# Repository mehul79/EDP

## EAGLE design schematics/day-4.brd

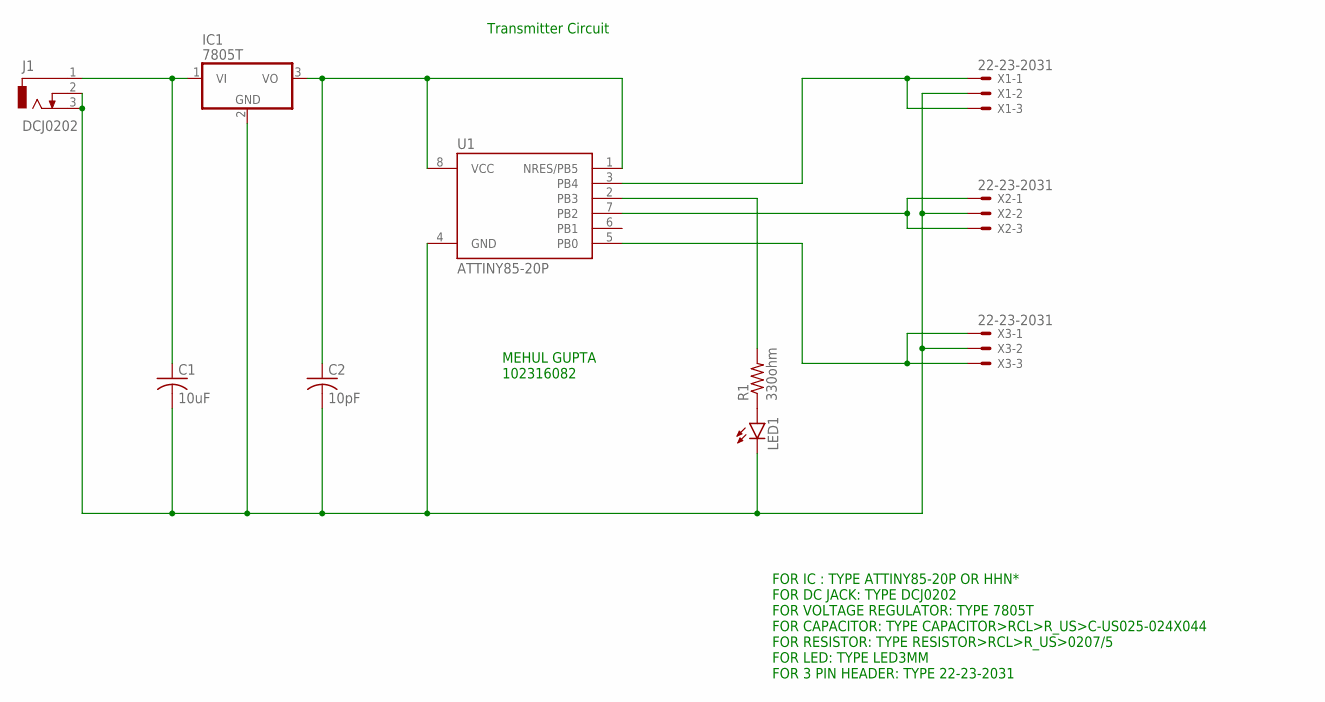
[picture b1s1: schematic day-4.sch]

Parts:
C1: 10uF; C025-024X044
C2: 10pF; C025-024X044
IC1: 7805T; TO220H
J1: DCJ0202
LED1: LED3MM
R1: 330ohm; 0204/5
U1: ATTINY85-20P; PDIP08_300MIL
X1, X2, X3: 22-23-2031

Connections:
unnamed: C1.1, IC1.1 (VI), J1.1
unnamed: C1.2, C2.2, IC1.2 (GND), J1.2, J1.3, LED1.K (C), U1.4 (GND), X1.2, X2.2, X3.2
unnamed: C2.1, IC1.3 (VO), U1.1 (NRES/PB5), U1.8 (VCC)
unnamed: U1.3 (PB4), X1.1, X1.3
unnamed: LED1.A, R1.1
unnamed: U1.7 (PB2), X2.1, X2.3
unnamed: R1.2, U1.2 (PB3)
unnamed: U1.5 (PB0), X3.1, X3.3

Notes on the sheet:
FOR IC : TYPE ATTINY85-20P OR HHN* FOR DC JACK: TYPE DCJ0202 FOR VOLTAGE REGULATOR: TYPE 7805T FOR CAPACITOR: TYPE CAPACITOR>RCL>R_US>C-US025-024X044 FOR RESISTOR: TYPE RESISTOR>RCL>R_US>0207/5 FOR LED: TYPE LED3MM FOR 3 PIN HEADER: TYPE 22-23-2031
Transmitter Circuit
MEHUL GUPTA 102316082

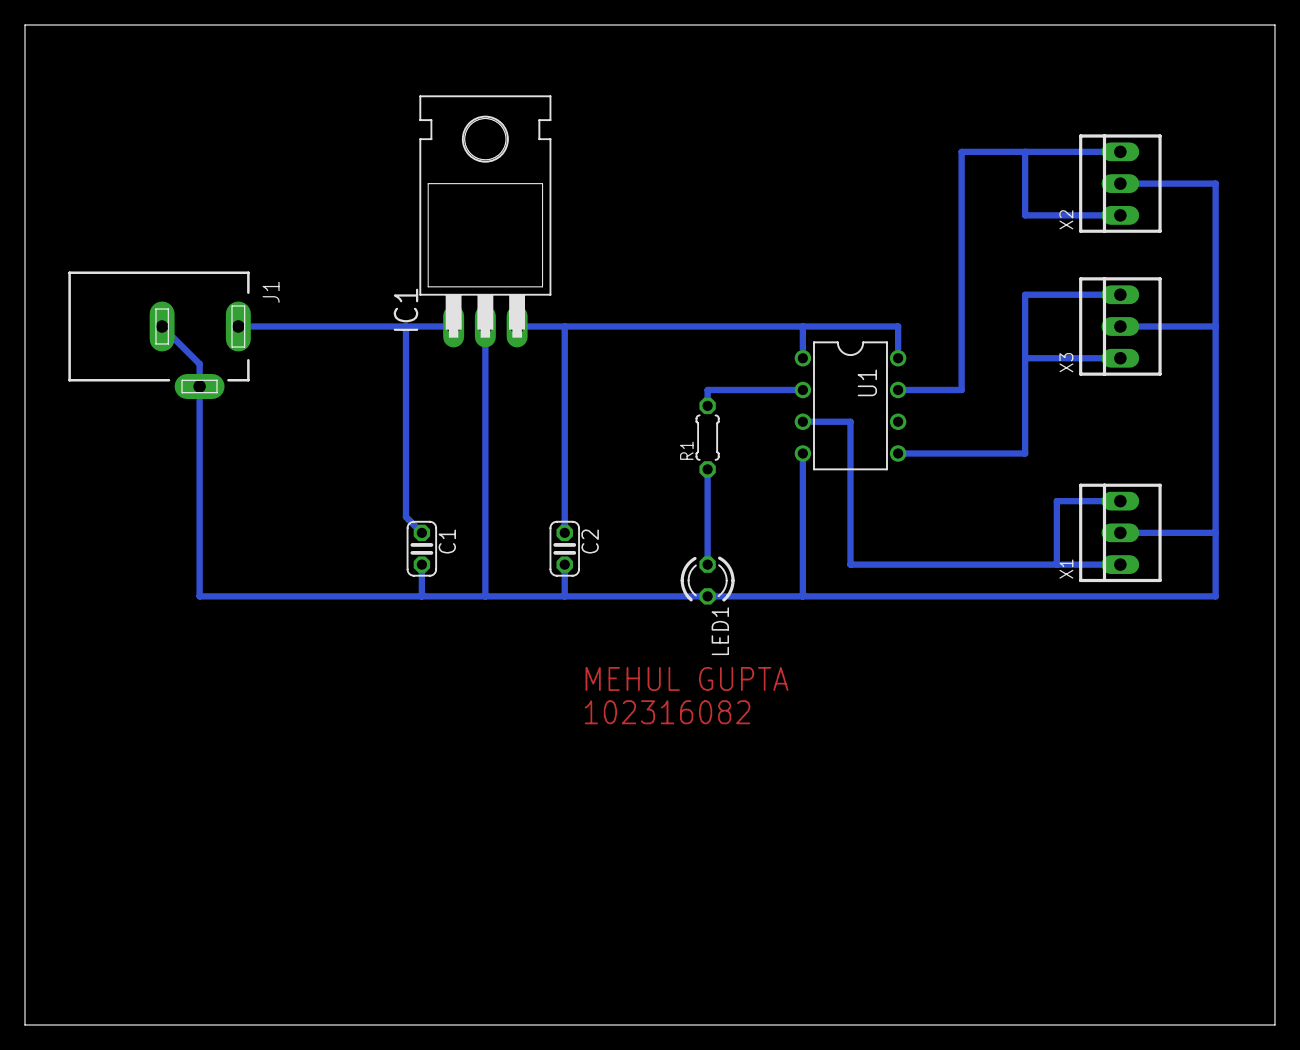
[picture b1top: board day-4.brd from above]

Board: 2 copper layers, 100.0 x 80.0 mm, 10 parts (0 on the bottom side), 8 nets.

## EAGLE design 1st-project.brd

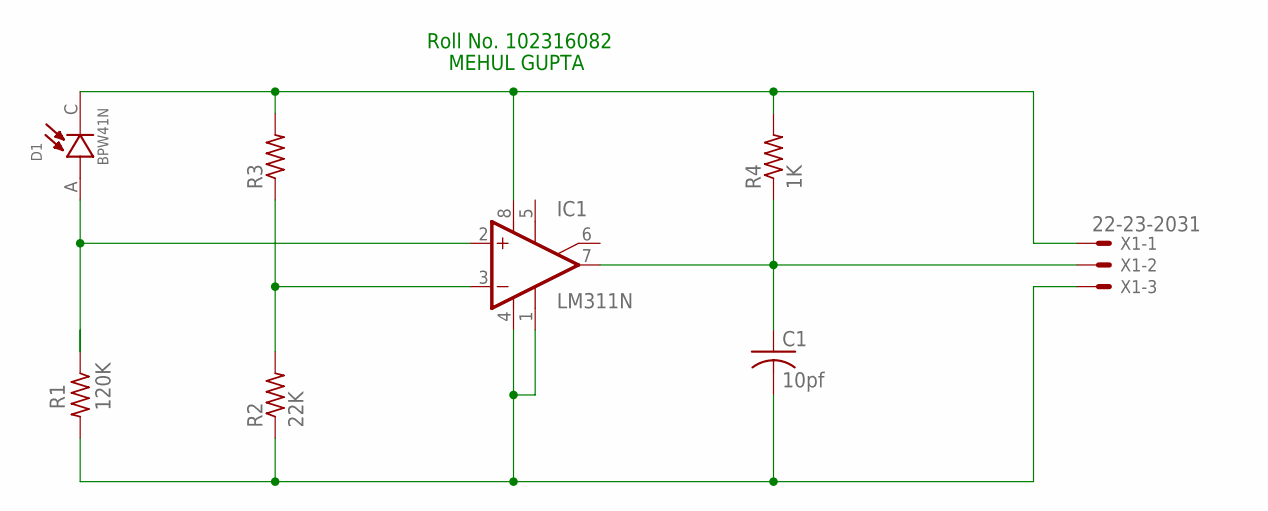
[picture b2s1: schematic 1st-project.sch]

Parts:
C1: 10pf; C025-024X044
D1: BPW41N; DIO_BPW41N
IC1: LM311N; DIL08
R1: 120K; 0204/5
R2: 22K; 0204/5
R3: R-US_0204/5; 0204/5
R4: 1K; 0204/5
X1: 22-23-2031

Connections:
unnamed: D1.A, IC1.2 (+IN), R1.1
unnamed: D1.C, IC1.8 (V+), R3.2, R4.2, X1.1
unnamed: C1.2, IC1.1 (GND), IC1.4 (V-), R1.2, R2.1, X1.3
unnamed: IC1.3 (-IN), R2.2, R3.1
unnamed: C1.1, IC1.7 (OUT), R4.1, X1.2

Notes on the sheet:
MEHUL GUPTA
Roll No. 102316082

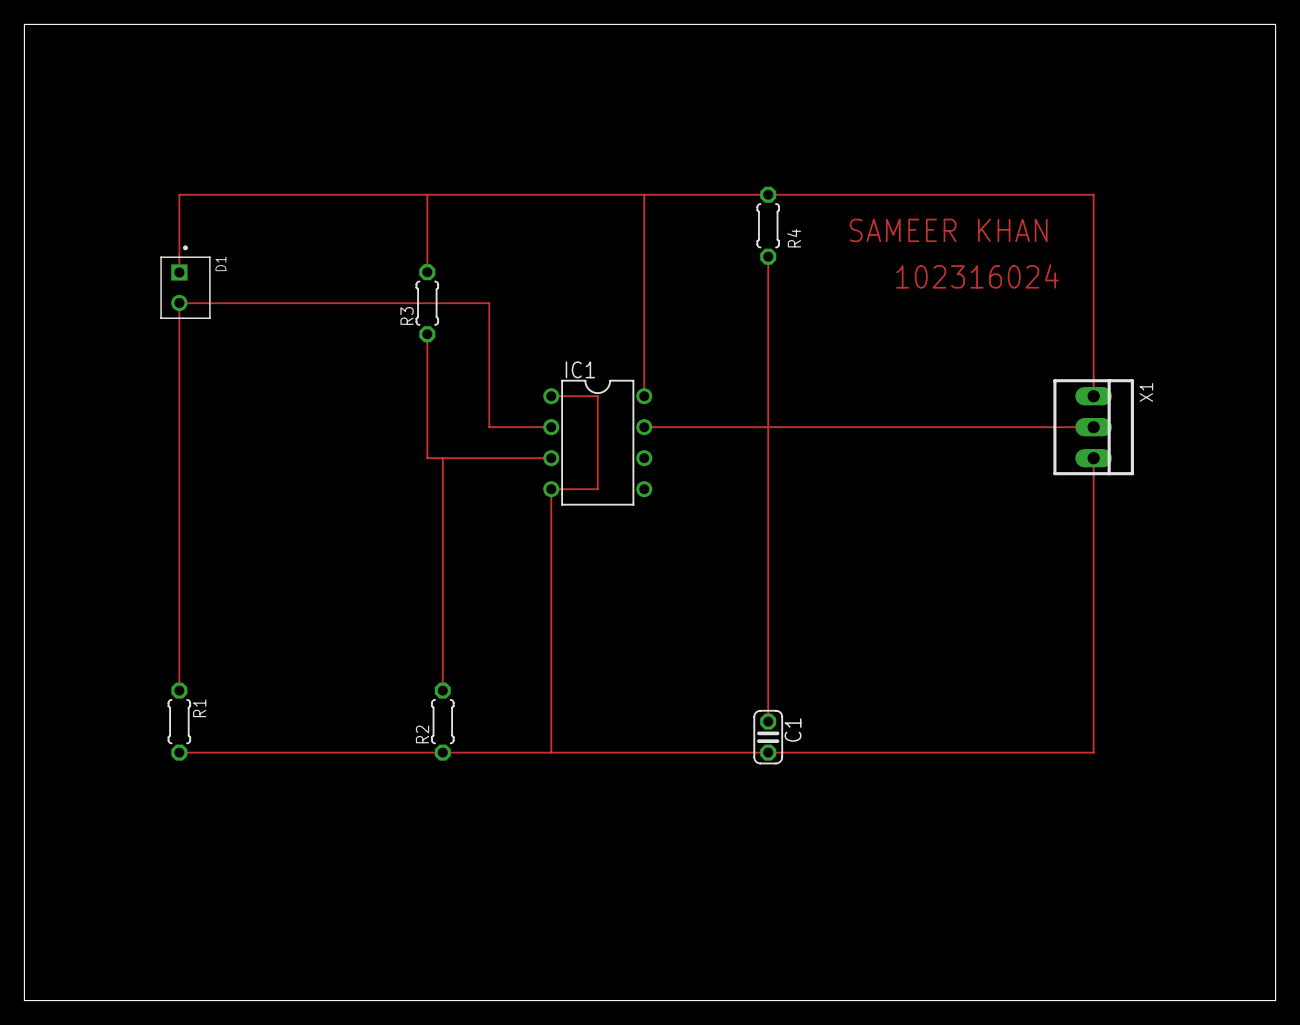
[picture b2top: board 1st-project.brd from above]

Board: 2 copper layers, 102.5 x 80.0 mm, 8 parts (0 on the bottom side), 5 nets.

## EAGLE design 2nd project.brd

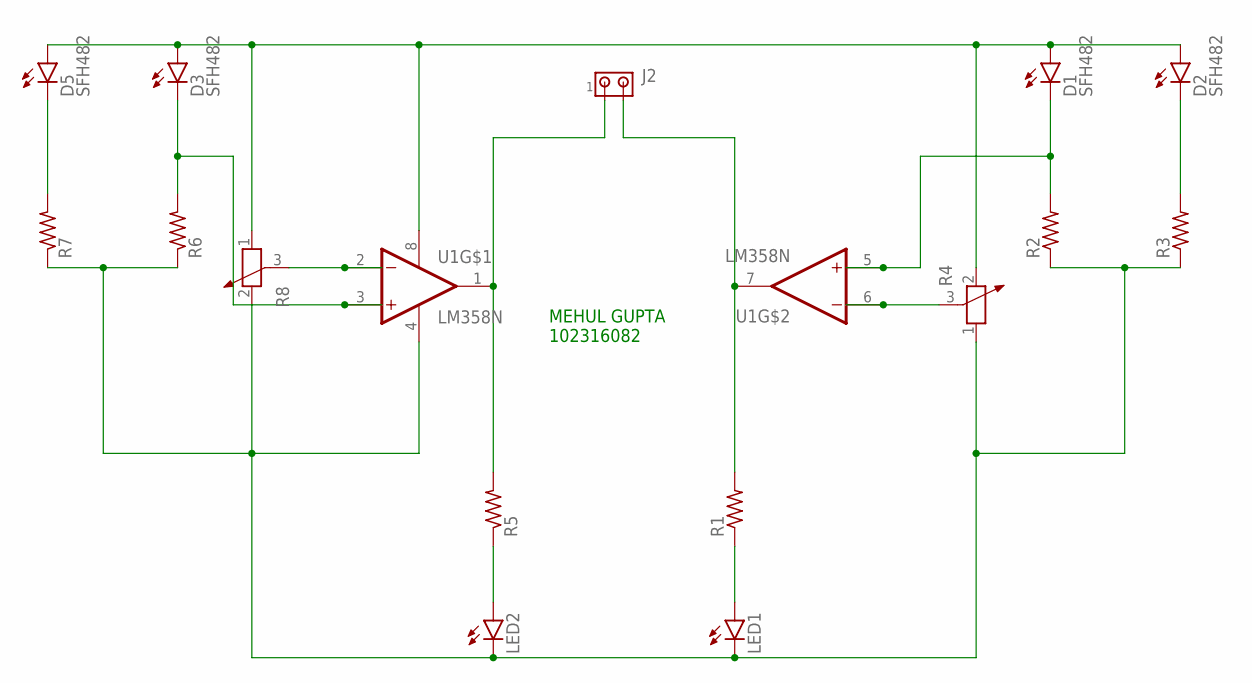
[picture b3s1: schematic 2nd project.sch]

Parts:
D1, D2, D3, D5: SFH482
J2: MTA02-100; 10X02MTA
LED1, LED2: LED3MM
R1, R2, R3, R5, R6, R7: R-US_0204/5; 0204/5
R4, R8: POTENTIOMETER_PT-10; PT-10
U1: LM358N; DIP762W46P254L960H508Q8

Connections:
unnamed: R4.3, U1.6 (2IN-)
unnamed: J2.2, R1.2, U1.7 (2OUT)
unnamed: D3.K (C), R6.2, U1.3 (1IN+)
unnamed: LED1.A, R1.1
unnamed: D2.K (C), R3.2
unnamed: D1.K (C), R2.2, U1.5 (2IN+)
unnamed: R8.3, U1.2 (1IN-)
unnamed: J2.1, R5.2, U1.1 (1OUT)
unnamed: LED2.A, R5.1
unnamed: LED1.K (C), LED2.K (C), R2.1, R3.1, R4.1, R6.1, R7.1, R8.2, U1.4 (GND)
unnamed: D1.A, D2.A, D3.A, D5.A, R4.2, R8.1, U1.8 (VCC)
unnamed: D5.K (C), R7.2

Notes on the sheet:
MEHUL GUPTA 102316082

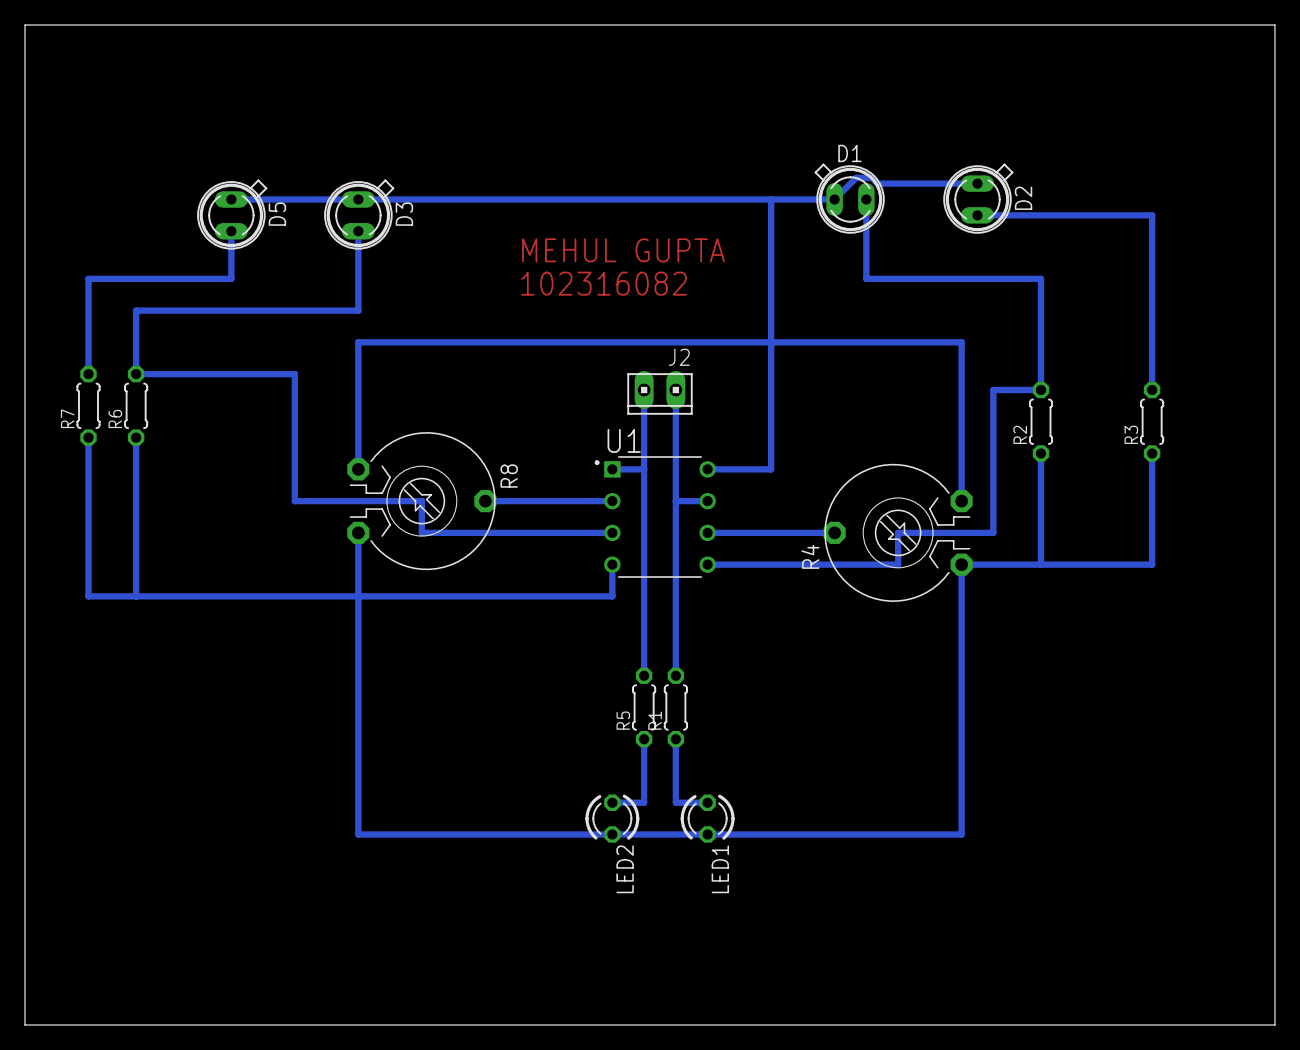
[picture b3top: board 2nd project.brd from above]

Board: 2 copper layers, 100.0 x 80.0 mm, 16 parts (0 on the bottom side), 12 nets.

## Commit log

2025-02-24 jkn-2
2025-05-05 change
2025-05-05 hehe
2025-05-19 some chnages
2025-05-19 code changes
